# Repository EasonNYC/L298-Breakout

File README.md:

L298-Breakout
=============
A simple breakout board for the L298N motor driver. Designed in Cadsoft Eagle.

Made by Eason Smith (Eason@EasonRobotics.com)

Further details can be found at:  

[http://www.easonrobotics.com/?portfolio=l298-breakout-board ](http://www.easonrobotics.com/?portfolio=l298-breakout-board)

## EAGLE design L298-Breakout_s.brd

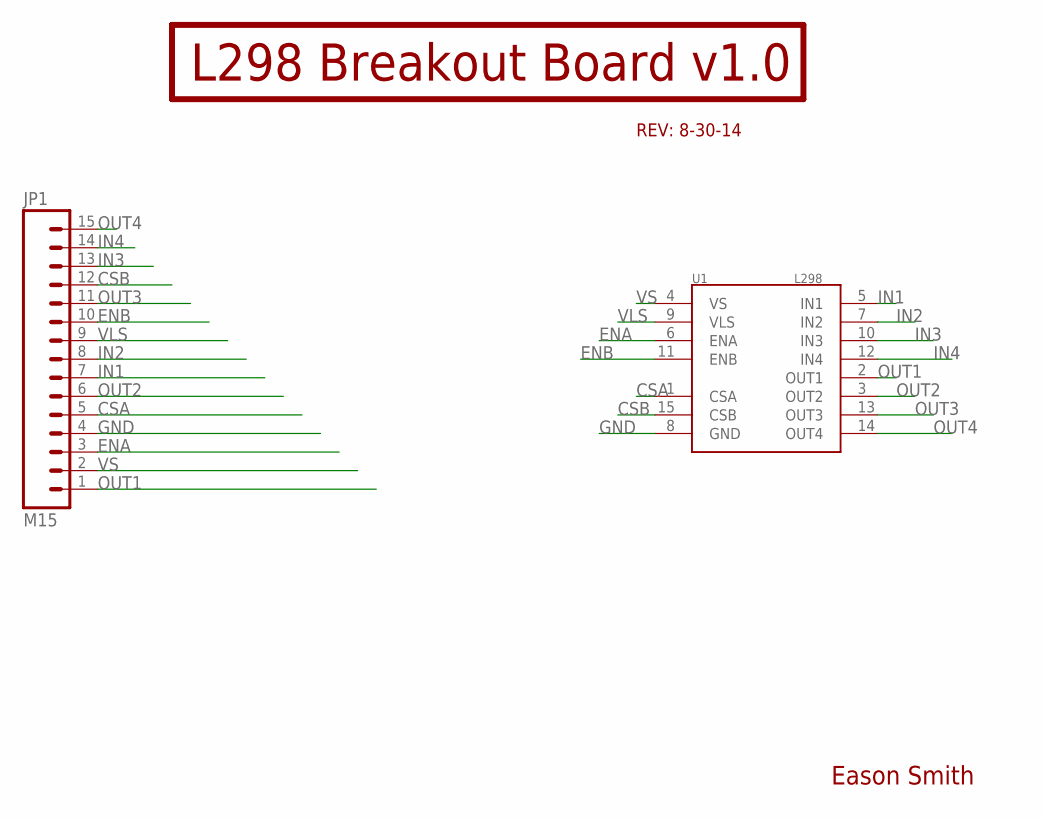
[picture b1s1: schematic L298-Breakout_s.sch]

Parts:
JP1: M15; 1X15
U1: L298; MULTIWATT15

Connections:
CSA: JP1.5, U1.1 (CSA)
CSB: JP1.12, U1.15 (CSB)
ENA: JP1.3, U1.6 (ENA)
ENB: JP1.10, U1.11 (ENB)
GND: JP1.4, U1.8 (GND)
IN1: JP1.7, U1.5 (IN1)
IN2: JP1.8, U1.7 (IN2)
IN3: JP1.13, U1.10 (IN3)
IN4: JP1.14, U1.12 (IN4)
OUT1: JP1.1, U1.2 (OUT1)
OUT2: JP1.6, U1.3 (OUT2)
OUT3: JP1.11, U1.13 (OUT3)
OUT4: JP1.15, U1.14 (OUT4)
VLS: JP1.9, U1.9 (VLS)
VS: JP1.2, U1.4 (VS)

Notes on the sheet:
Eason Smith
REV: 8-30-14
L298 Breakout Board v1.0

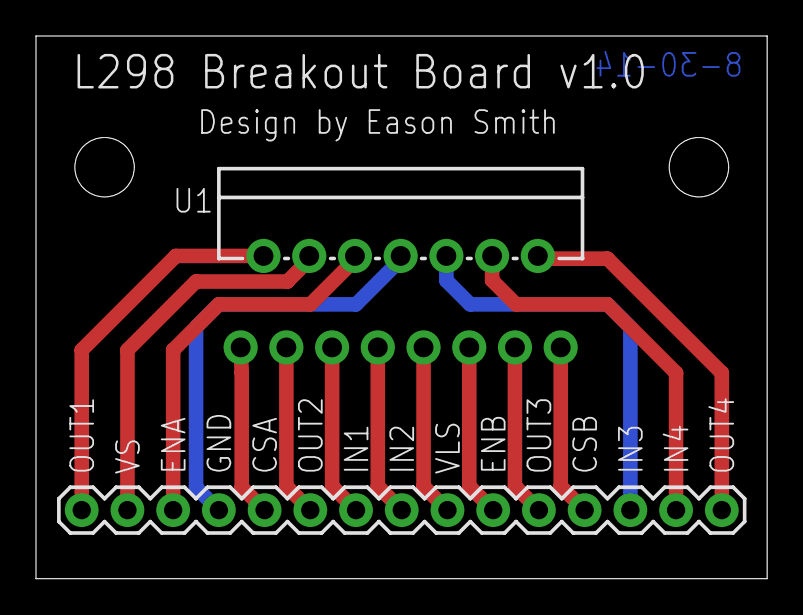
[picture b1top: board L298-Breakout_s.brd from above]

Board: 2 copper layers, 40.6 x 30.1 mm, 4 parts (0 on the bottom side), 15 nets.

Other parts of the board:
U$1, U$2: STAND-OFF

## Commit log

2014-09-13 :lollipop: Added .gitattributes
2014-09-13 init commit
2014-09-13 Added web address
2016-01-10 deleted .gitattributes

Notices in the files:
parts and their libraries:
SparkFun-PowerIC: Licensing: Creative Commons ShareAlike 4.0 International - https://creativecommons.org/licenses/by-sa/4.0
